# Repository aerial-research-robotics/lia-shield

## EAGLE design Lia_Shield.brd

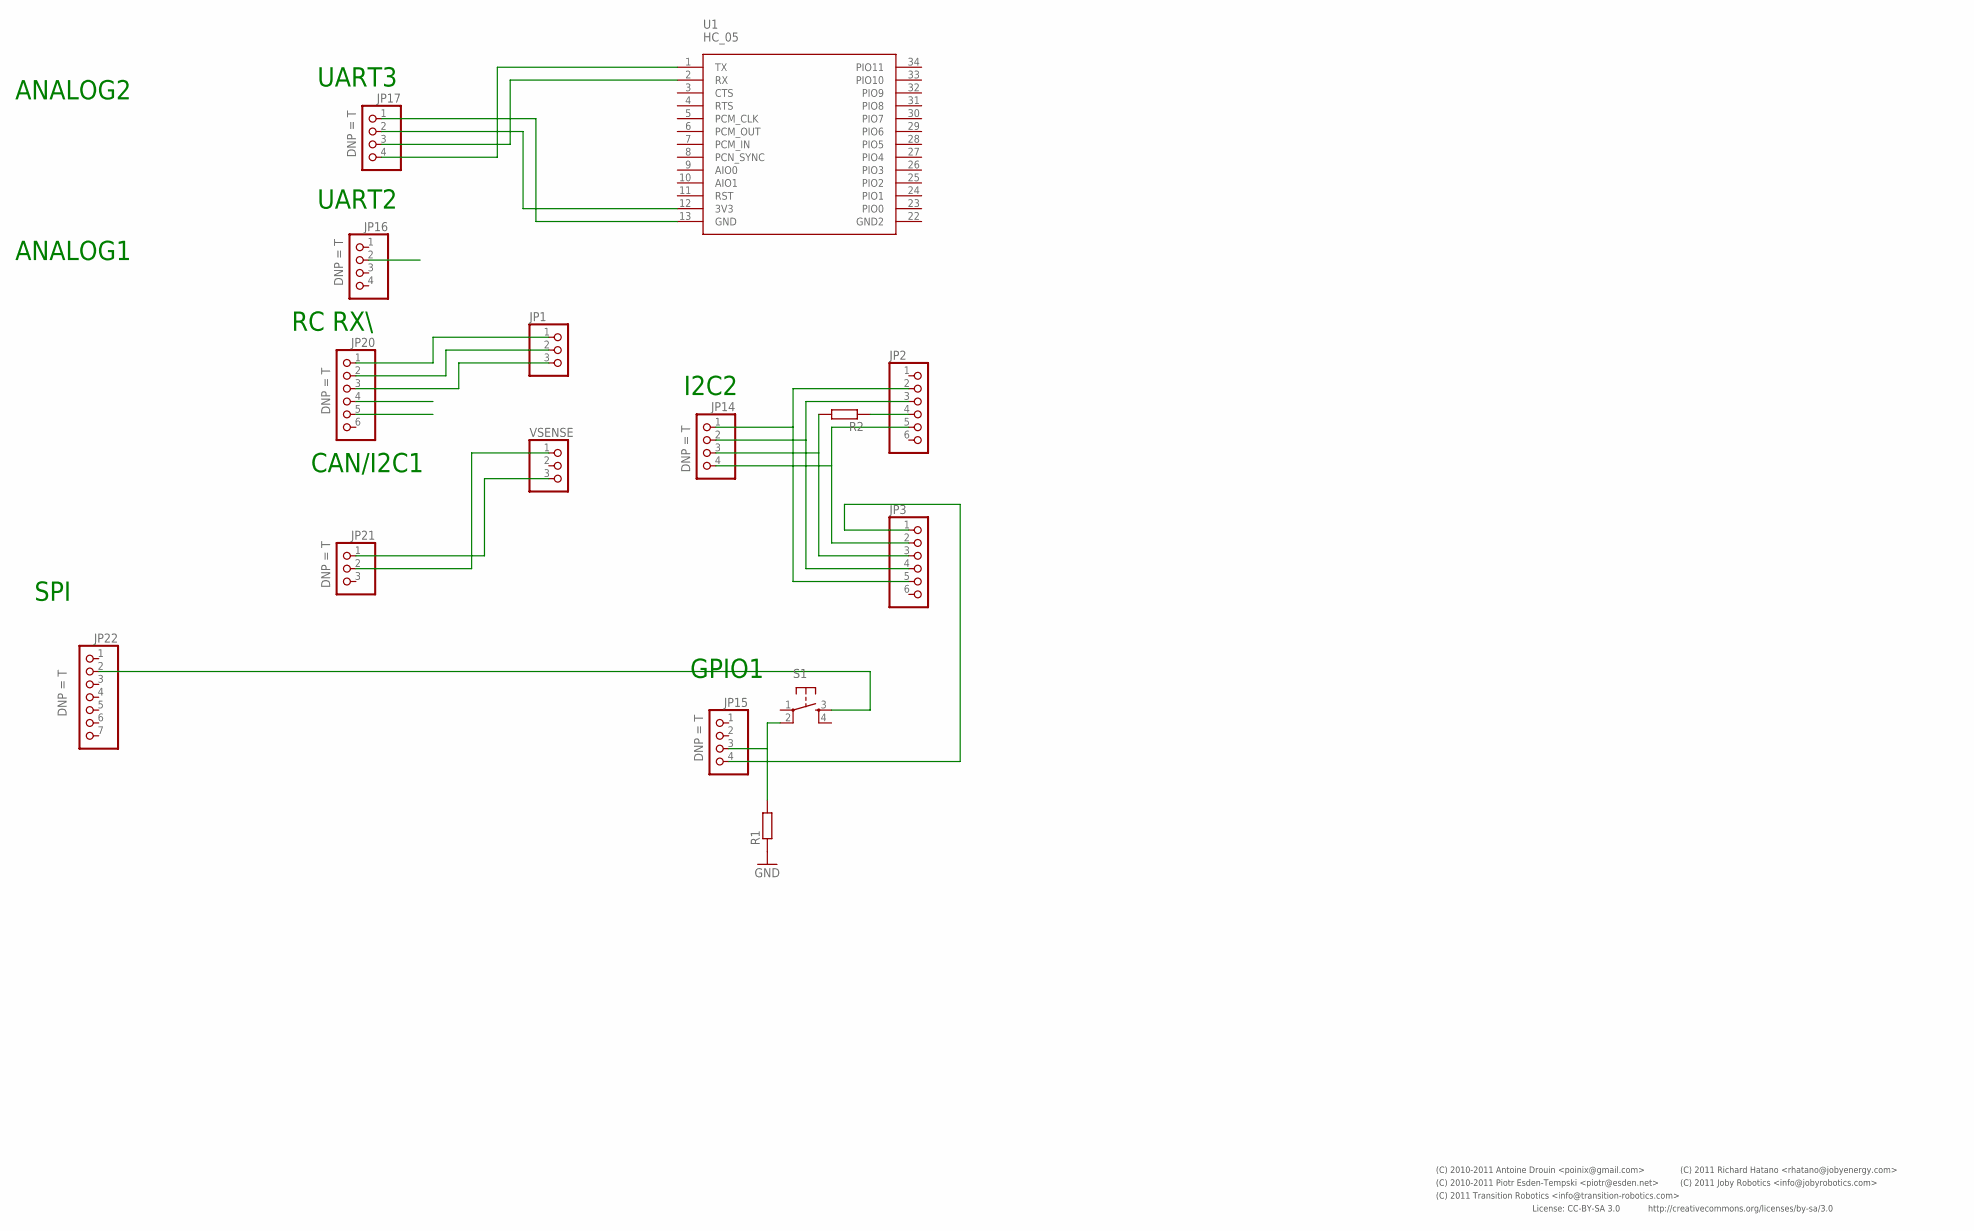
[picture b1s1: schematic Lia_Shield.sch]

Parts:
JP1: PINHD-1X3/90; 1X03/90
JP2, JP3: PINHD-1X6; 1X06
JP14, JP15, JP16, JP17: PINHD-1X4; 1X04; PARTNO conn-th-0.1in-4-1
JP20: PINHD-1X6; 1X06; PARTNO conn-th-0.1in-6-1
JP21: PINHD-1X3; 1X03; PARTNO conn-th-0.1in-7-1
JP22: PINHD-1X7; 1X07; PARTNO conn-th-0.1in-7-1
R1, R2: R-EU_R1206; R1206
S1: TAC_SWITCHPTH; TACTILE-PTH
U1: HC_05; BLUETOOTH_SMD
VSENSE: PINHD-1X3/90; 1X03/90

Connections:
GND: JP1.1, JP20.1, JP20.4
unnamed: JP21.2, VSENSE.1
unnamed: JP1.3, JP20.3
unnamed: JP17.3, U1.2 (RX)
unnamed: JP17.4, U1.1 (TX)
unnamed: JP3.3, JP14.3, R2.2
unnamed: JP2.5, JP3.2, JP14.4
unnamed: JP3.1, JP15.4
unnamed: JP15.3, R1.2, S1.2
unnamed: JP2.4, R2.1
RC1: JP2.2, JP3.5, JP14.1, JP17.1, JP21.1, R1.1, U1.13 (GND), VSENSE.3
VCC: JP1.2, JP2.3, JP3.4, JP14.2, JP16.2, JP17.2, JP20.2, JP20.5, JP22.2, S1.3, U1.12 (3V3)

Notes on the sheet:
SPI
I2C2
ANALOG2
ANALOG1
GPIO1
UART3
UART2
RC RX\
CAN/I2C1
License: CC-BY-SA 3.0
http://creativecommons.org/licenses/by-sa/3.0
(C) 2010-2011 Piotr Esden-Tempski <piotr@esden.net>
(C) 2010-2011 Antoine Drouin <poinix@gmail.com>
(C) 2011 Richard Hatano <rhatano@jobyenergy.com>
(C) 2011 Joby Robotics <info@jobyrobotics.com>
(C) 2011 Transition Robotics <info@transition-robotics.com>

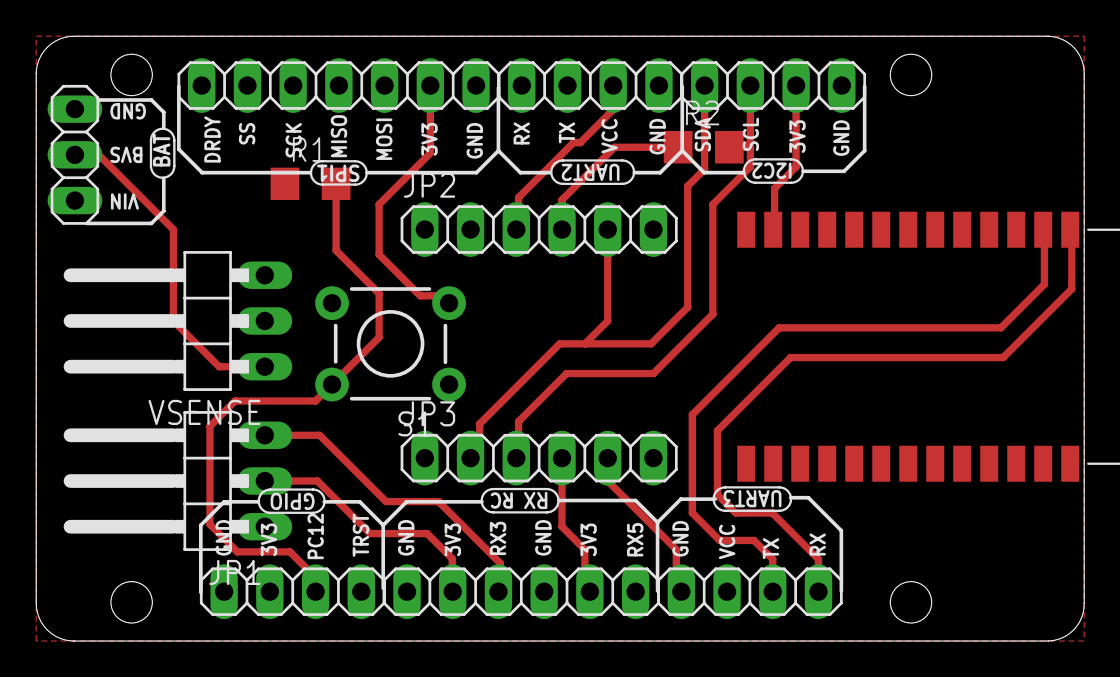
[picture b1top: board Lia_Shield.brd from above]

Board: 4 copper layers, 58.2 x 33.6 mm, 15 parts (0 on the bottom side), 12 nets.

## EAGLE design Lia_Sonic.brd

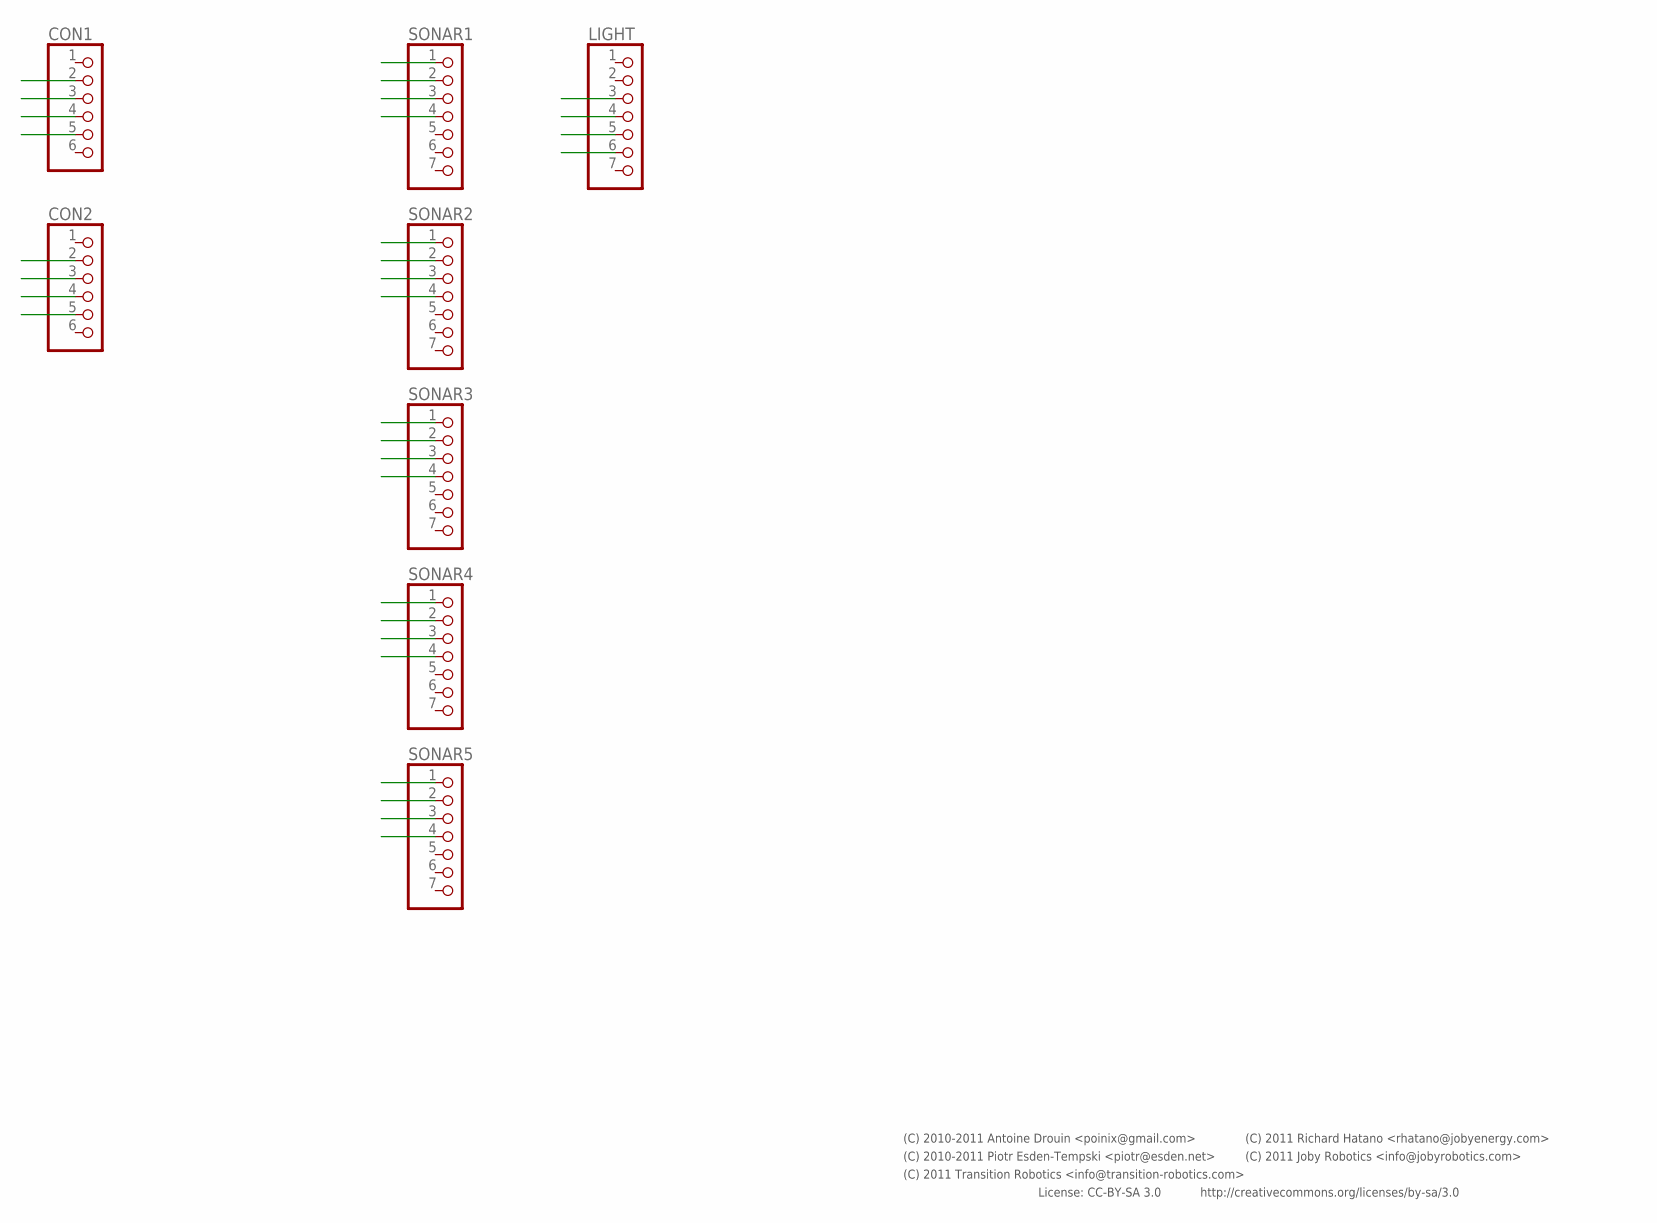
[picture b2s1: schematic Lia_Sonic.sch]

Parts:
CON1, CON2: PINHD-1X6; 1X06
LIGHT: PINHD-1X7; 1X07
SONAR1, SONAR2, SONAR3, SONAR4, SONAR5: PINHD-1X7; 1X07

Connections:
GND: CON1.2, CON2.5, LIGHT.6, SONAR1.1, SONAR2.1, SONAR3.1, SONAR4.1, SONAR5.1
SCL: CON1.4, CON2.3, LIGHT.4, SONAR1.3, SONAR2.3, SONAR3.3, SONAR4.3, SONAR5.3
SDA: CON1.5, CON2.2, LIGHT.3, SONAR1.4, SONAR2.4, SONAR3.4, SONAR4.4, SONAR5.4
VCC: CON1.3, CON2.4, LIGHT.5, SONAR1.2, SONAR2.2, SONAR3.2, SONAR4.2, SONAR5.2

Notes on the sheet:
License: CC-BY-SA 3.0
http://creativecommons.org/licenses/by-sa/3.0
(C) 2010-2011 Piotr Esden-Tempski <piotr@esden.net>
(C) 2010-2011 Antoine Drouin <poinix@gmail.com>
(C) 2011 Richard Hatano <rhatano@jobyenergy.com>
(C) 2011 Joby Robotics <info@jobyrobotics.com>
(C) 2011 Transition Robotics <info@transition-robotics.com>

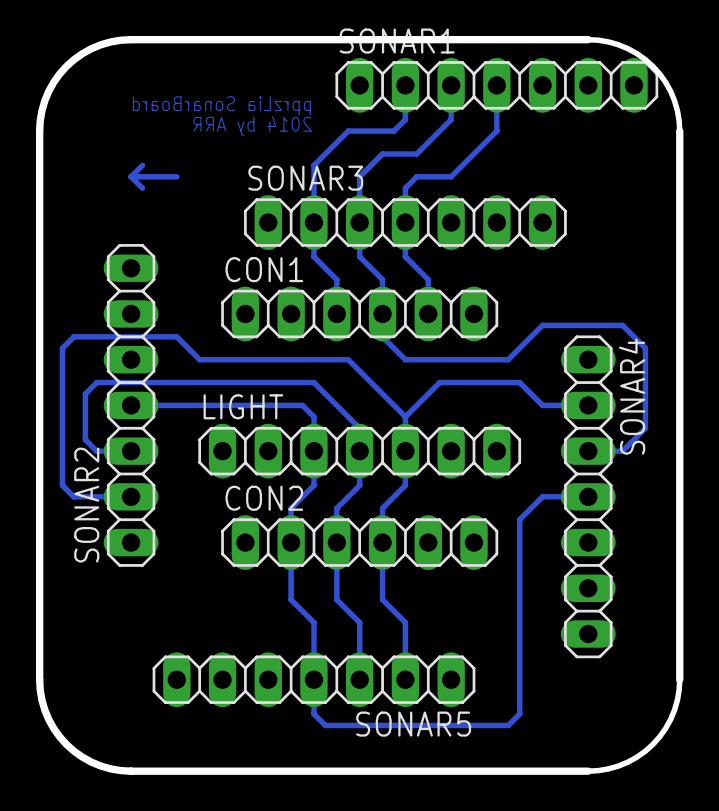
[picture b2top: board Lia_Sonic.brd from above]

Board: 4 copper layers, 35.6 x 40.6 mm, 8 parts (0 on the bottom side), 4 nets.

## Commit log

2014-01-09 angled receiver connector
2014-01-10 david wollte es so
2014-01-11 comitting scheiß

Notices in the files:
parts and their libraries:
SparkFun-Electromechanical: Licensing: CC v3.0 Share-Alike You are welcome to use this library for commercial purposes.
